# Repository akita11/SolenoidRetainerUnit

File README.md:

# SolenoidRetainerUnit

[タカハのスリムロック](https://www.takaha.co.jp/co/product-slim-lock/)等の負荷を、「最初短い時間通電したあとは、弱く通電する」という制御を行います。スリムロックでは、通電するとロックが解除されますが、通電を解除すると、再び押し込めばロックされます。「ロックが解除された状態を維持したいが、通電しつづけると負荷に負担がかかる（スリムロックは長時間通電すると、内部の部品が熱で変形して使えなくなります）」という場合に。PWM駆動で「弱く通電した状態」を維持します。（[スイッチサイエンスで委託販売中](https://www.switch-science.com/products/9147)です）

基板形状が「[M5Stack用VH3.96-4ピンユニット](https://www.switch-science.com/products/4055)」と同一のため、そのケースを使うことができます。

## 使い方

オレンジ色のコネクタ(VH3.96-4p)に、負荷用の電源と負荷を接続します。M5Stackの[BAVGソケット](https://www.switch-science.com/products/7234)を使うと、電源は2.1mmプラグ、負荷はスプリング端子で接続できて便利です。

Grove端子のピン配置は以下のとおりです。
- 1. GND
- 2. VDD(3.3〜5V)
- 3. 未使用（内部でVDDにプルアップ）
- 4. 制御入力（内部でVDDにプルアップ）

「4.制御入力」を"0"にすると、最初の200msだけ負荷をONにし、そのあとは、「4.制御入力」が"0"の間はデューティー比10%でPWM駆動します。「4.制御入力」を"1"（または開放）とすると、負荷をOFFにします。

## プログラムの書き換え

このボードは、回路図をみるとわかるように、マイコン(STC8G1K08A)と負荷駆動用のMOSFETからなります。つまりマイコンのプログラム次第で、負荷を自由に制御することができます。

初期状態で書き込んであるプログラムはフォルダFW以下にありますので、必要であればこれを元に改造してください。Grove端子の2本の信号線はマイコンのUART端子につなげてあります。

マイコンSTC8G1K08Aのプログラム開発・書き込みは[こちらの記事](https://note.com/akita11/n/n41316faaaf19)などを参考にしてください。

## Author

Junichi Akita (akita@ifdl.jp, @akita11)

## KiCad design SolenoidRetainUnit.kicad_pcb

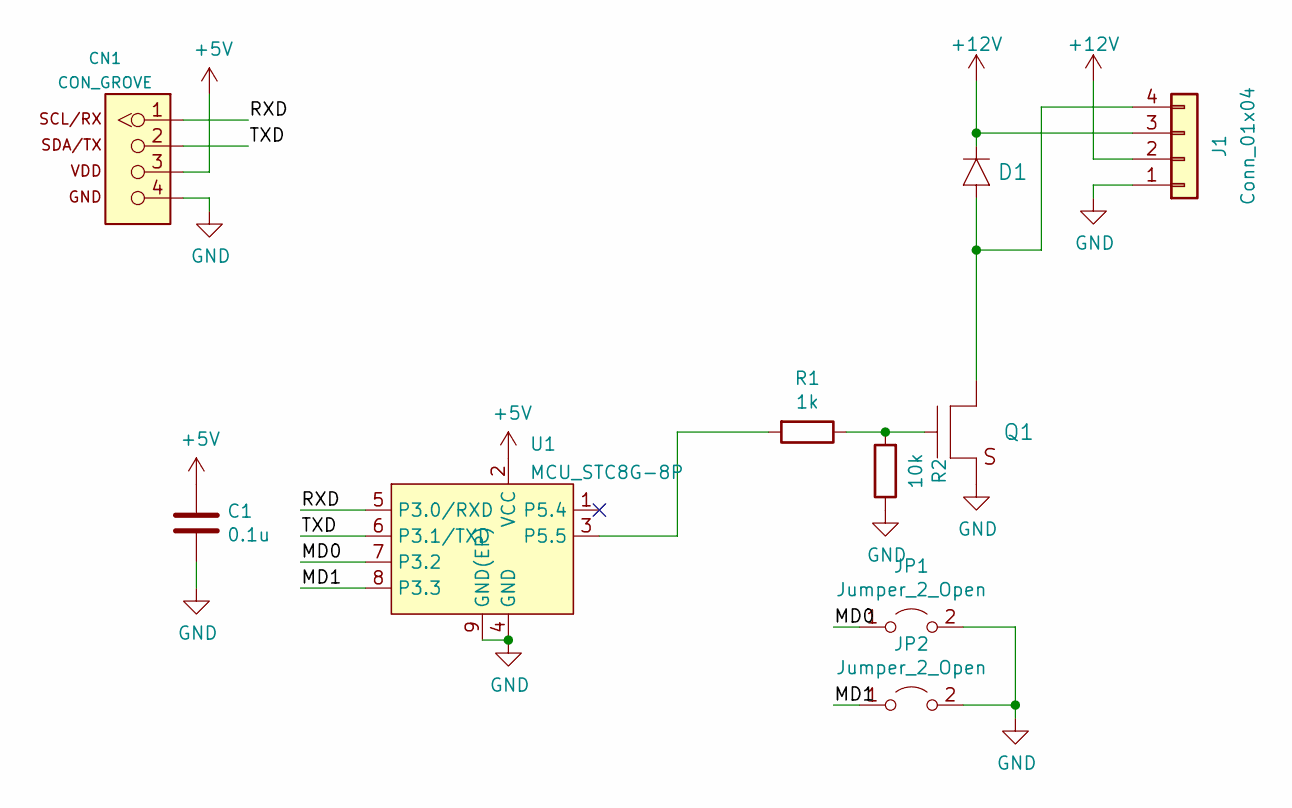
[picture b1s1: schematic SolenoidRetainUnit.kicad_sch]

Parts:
C1: 0.1u; C_0603_1608Metric; LCSC C14663
CN1: CON_GROVE; CON_GROVE_H
D1: DIODE; D_SOD123FL; LCSC C2760867
J1: Conn_01x04; JST_VH_S4P-VH_1x04_P3.96mm_Horizontal
JP1, JP2: Jumper_2_Open; SolderJumper-2_P1.3mm_Open_Pad1.0x1.5mm
Q1: TR_NMOS_IRLML6344; SOT-23; LCSC C20917
R1: 1k; R_0603_1608Metric; LCSC C22764
R2: 10k; R_0603_1608Metric; LCSC C25804
U1: MCU_STC8G-8P; DFN-8-1EP_3x3mm_P0.5mm_EP1.65x2.38mm; LCSC C915664

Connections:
+5V: C1.1, CN1.3, U1.2 (VCC)
+12V: D1.K, J1.2, J1.3
/MD0: JP1.1 (A), U1.7 (P3.2)
/MD1: JP2.1 (A), U1.8 (P3.3)
/RXD: CN1.1, U1.5 (P3.0/RXD)
/TXD: CN1.2, U1.6 (P3.1/TXD)
GND: C1.2, CN1.4, J1.1, JP1.2 (B), JP2.2 (B), Q1.2 (S), R2.1, U1.4 (GND), U1.9 (GND(EP))
unnamed: D1.A, J1.4, Q1.3 (D)
unnamed: Q1.1 (G), R1.1, R2.2
unnamed: R1.2, U1.3 (P5.5)

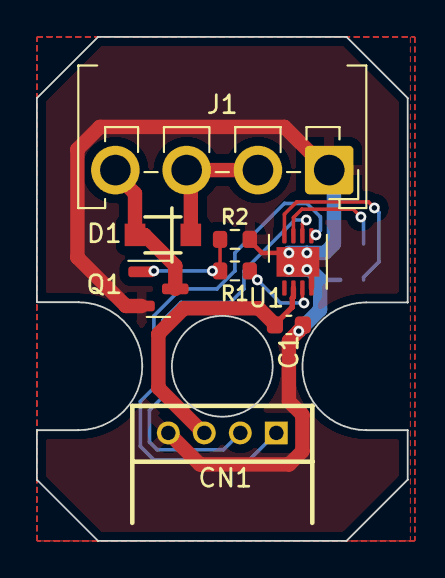
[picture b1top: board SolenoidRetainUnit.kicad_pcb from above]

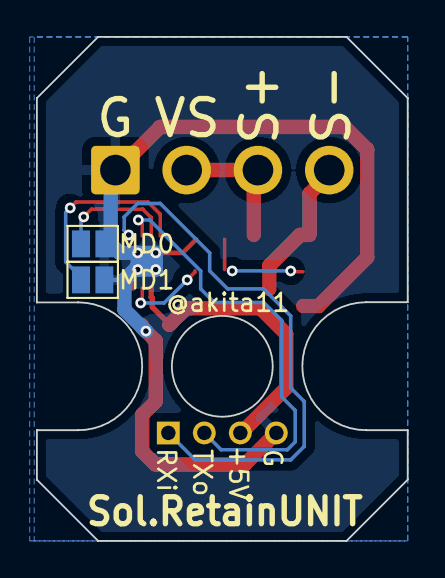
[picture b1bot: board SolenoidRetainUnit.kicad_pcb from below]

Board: 2 copper layers, 20.6 x 28.0 mm, 10 parts (2 on the bottom side), 10 nets.
